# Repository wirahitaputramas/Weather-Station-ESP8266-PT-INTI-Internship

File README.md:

# Weather Station ESP8266

# Overview

<div align="center">
  
</div>
<div align="center">
  
</div>

<div align="center">
  
</div>
<div align="center">
  
</div>

The repository includes everything needed to build an Weather Station ESP8266 (including hardware information, PCB Design, and footprint):

# What do I Need To Make One?
In this project, we assume that we still need to debug and see the output in serial monitor. So we need :
- Arduino IDE (the lastest version recommended) with serial monitor in PC or Laptop

Other Essential Things :
- Standar USB to Micro USB cable
- ESP-12E Development Board ESP8266 NodeMCU ([Pict](https://raw.githubusercontent.com/wirahitaputramas/Weather-Station-ESP8266-PT-INTI-Internship/master/images/ESP%2012E%20Development%20Board.jpg "ESP-12E Development Board ESP8266 NodeMCU"))
- OLED I2C Display 128x64 Pixel ([Pict](https://raw.githubusercontent.com/wirahitaputramas/Weather-Station-ESP8266-PT-INTI-Internship/master/images/OLED%20I2C%20Display.jpg "OLED I2C Display 128x64 Pixel"))
- SPI MicroSD Module ([Pict](https://raw.githubusercontent.com/wirahitaputramas/Weather-Station-ESP8266-PT-INTI-Internship/master/images/MicroSD%20Modul.jpg "MicroSD Module"))
- MicroSD Card (SDHC Under 32 GB recommended)
- DHT22 Modue ([Pict](https://raw.githubusercontent.com/wirahitaputramas/Weather-Station-ESP8266-PT-INTI-Internship/master/images/DHT22%20Module.jpgg "DHT22 Module"))
- LDR Photoresistor
- SMD Resistor 5 kohm

# How to Make One ?

## Testing and Prototyping on Breadboard
Before we make the circuit on the PCB, we must ensure that we choose the correct GPIO. Because of that, first of all we must hookup all component on breadboard like this picture below :
<div align="center">
  
</div>

Here is the raw fritzing file ([Fritzing](https://github.com/wirahitaputramas/Weather-Station-ESP8266-PT-INTI-Internship/blob/master/Weather%20Station%20ESP8266%20on%20Breadboard.fzz "Weather Station ESP8266 on Breadboard"))

Here is the connection of each pin (exclude Vcc & GND) :
- D1 or GPIO5 to OLED SCL
- D2 or GPIO4 to OLED SDA
- D4 or GPIO2 to DHT22 IO (Data)
- D5 or GPIO14 to microSD SCLK
- D6 or GPIO12 to microSD MISO
- D7 or GPIO13 to microSD MOSI
- D8 or GPIO15 to microSD CS
- A0 or ADC0 to LDR Photoresistor

After finish the wiring, just prepare to upload the arduino whole program. We will modify any part of the source code in this repository

1. make sure that you have included the NTP Library from Fabrice Weinberg in the same folder with .ino file. Here is the [NTP Library Fabrice Weinberg](https://github.com/arduino-libraries/NTPClient.git "NTP Library Fabrice Weinberg")

2. Write down your WiFi Accses Point identity in IoT Property Block Code

```
/* IoT Property */
#include <ESP8266WiFi.h>
const char *ssid =  "SSID";     // replace with your wifi ssid and wpa2 key
const char *pass =  "PASS";
WiFiClient client;
```
3. Make your project channel in Thingspeak platform. Allocate three fields to store three different sensor reading data. After that get your channel ID and API key of your project channel. In the Screenshot below, the blue scratch is the channel ID, and the red scratch is the API Key
<div align="center">
  
</div>

Write down your Thingspeak Channel identity in Thingspeak Property Block Code in the source code.ino
```
/* Thingspeak Property */
#include <ThingSpeak.h>
unsigned long myChannelNumber = 823396; //Replace with your channel number
const char * myWriteAPIKey = "API KEY"; //Replace with your API key
/* End of Thingspeak Property */
```

4. Make sure all of pin assign in the source code.ino related to your wiring on breadboard

5. After finish uploading the program. Open the serial monitor and set the baud rate at 115200. Make sure there's no "nan" value. The nan value sometimes appear at DHT22 reading value. To Fix that, just try to plug and unplug again the DHT22 until the exact value appear, or you can trigger the DHT22 by connecting the Vcc pin to 5V

## PCB Desain, Assembly The Final Design, And Run the Weather Station on PCB

After the Prototyping on breadboard finish, now we can design the PCB on KiCad. 

1. First you need to make the Schematic or diagram of your circuit including the connection between each pin in ESP8266 and all the others component.

In this repo, you can get all file you need if you just want to skip this step. Find all .lib files. Those are your symbol schematic library. Our team have made those symbols from the scratch by seeing the datasheet and the real component. But we strongly recommended to learn and try make your own symbol because sometimes the symbol library from the other author doesn't match with your real component, usually it's pin arrangement. This is our schematic
<div align="center">
  
</div>

Use the label method instead of wiring method to make connection between each pin and don't forget to give some outline and comment information

2. Test The connection, and if no error, assign the footprint of each component
In this repo, we have included all footprint of the project, so you can just find the .preety folder and use that. Please note that our concept in this project is just soldering some female pin socket instead of directly solder each pin of component. So in the future, if the component broken you can easily replace with the other new one.

3. Placing and Tracking the PCB
Actually, this process depend on your own preference in placing and route the PCB. It isn't a problem if you try this step and find that your PCB is different with our PCB below, because the importnt things is all ratnest disappear and all the pin connection is right

<div align="center">
  
</div>

We choose a single layer instead of double layer because in our place double layer PCB more exspensive even when you compare with a huge single layer PCB. And also in our place, The manufacture and Printing Machine only support minimum track size at 0.6 mm and hole or drill diameter at 0.4 mm

4. After Finish the PCB. Generate the Greber File (as already available in this repo). Those picture below are some configuration to generate the gerber and drill file of our PCB
<div align="center">
  
</div>
<div align="center">
  
</div>

5. Print the PCB with Gerber File. Actually I just give those gerber and drill file and don't know the exact process of PCB printing. But i see the PCB printing employee use corel draw to process the greber file.

This first image is our PCB before soldering process
<div align="center">
  
</div>

<div align="center">
  
</div>

The  image is our PCB after soldering process

<div align="center">
  
</div>

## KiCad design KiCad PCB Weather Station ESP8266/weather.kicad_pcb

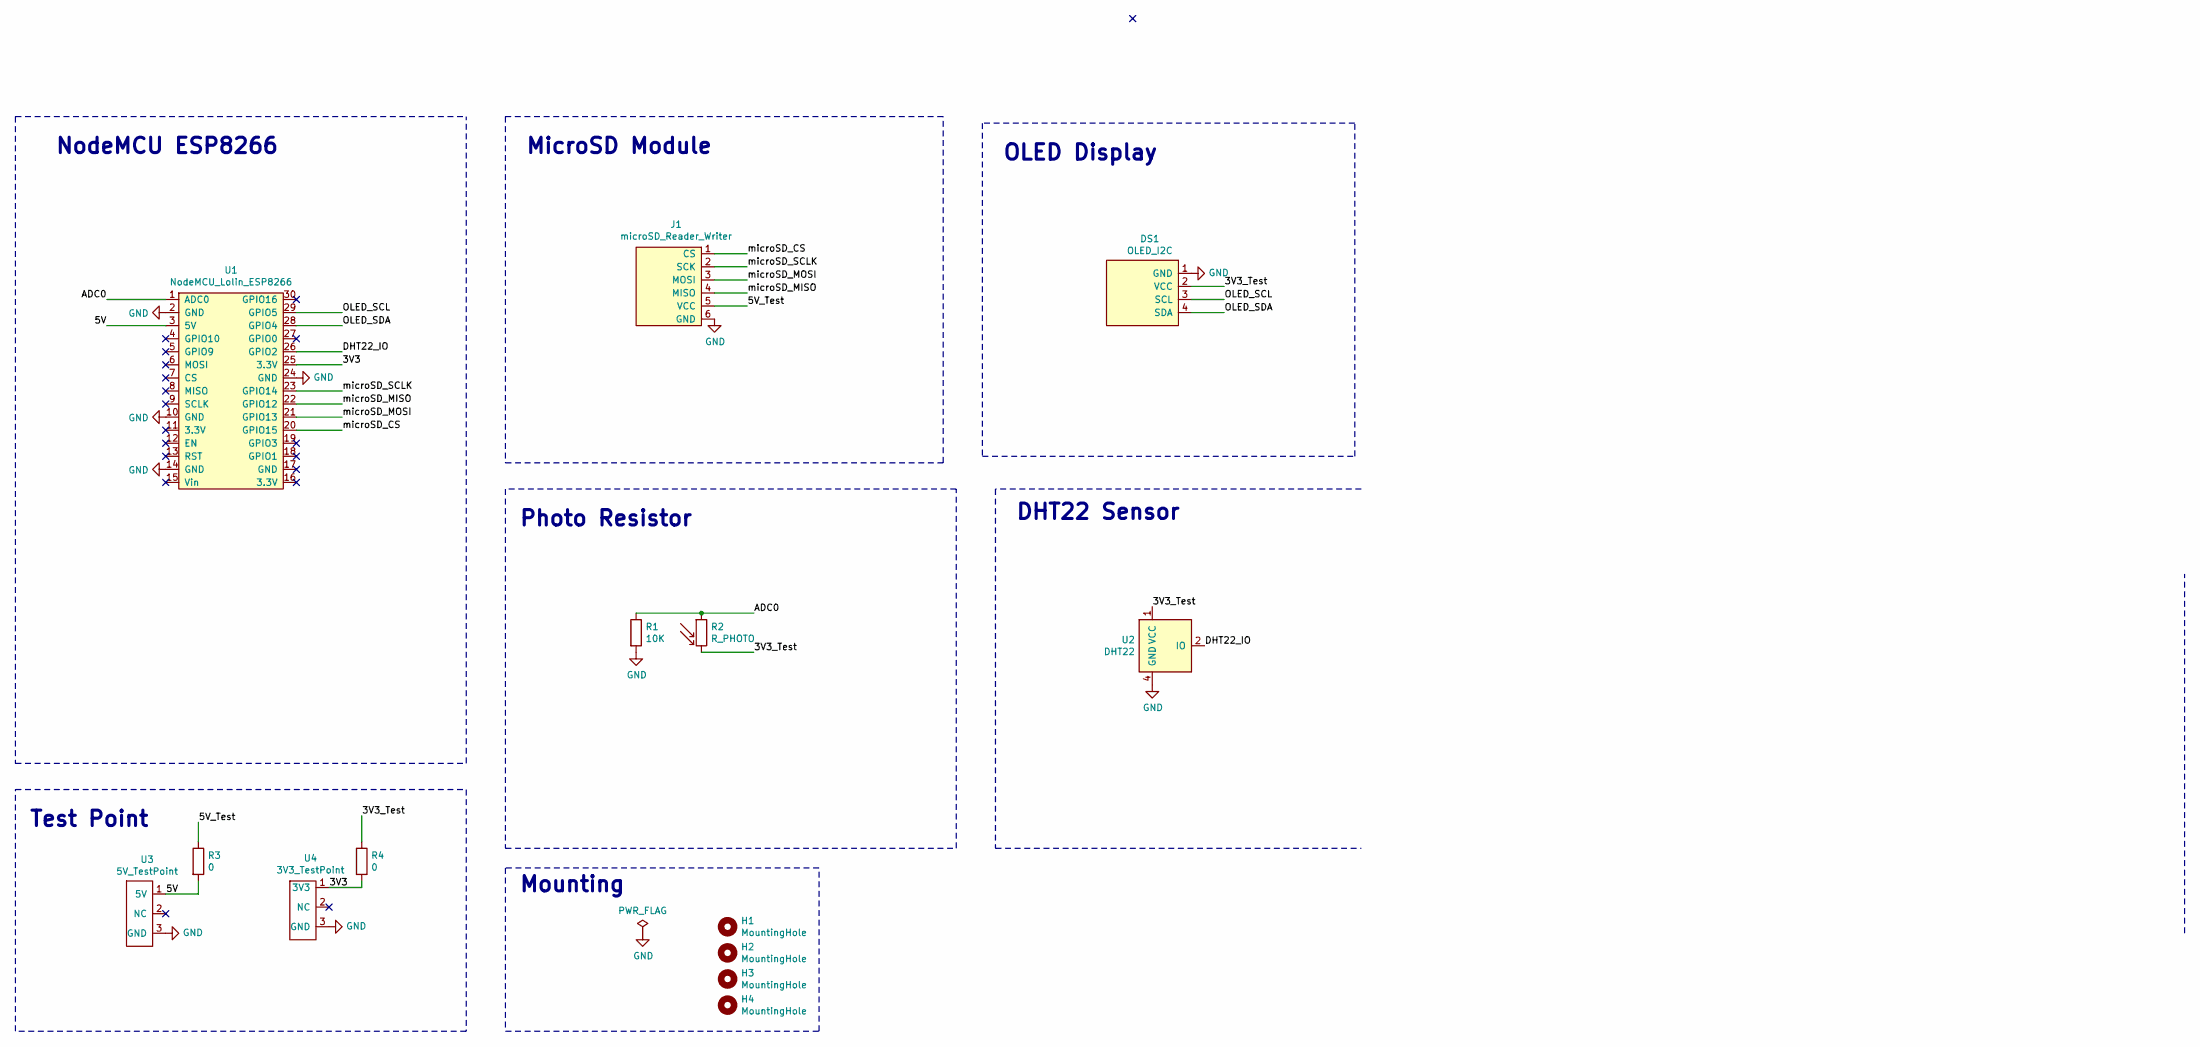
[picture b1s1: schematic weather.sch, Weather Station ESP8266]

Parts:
DS1: OLED_I2C
H1, H2, H3, H4: MountingHole; MountingHole_3.2mm_M3_DIN965
J1: microSD_Reader_Writer; MicroSD_Card_Modul
R1: 10K; R_0805_2012Metric
R2: R_PHOTO; PhotoResistor_THT_Horizontal
R3, R4: 0; R_0805_2012Metric
U1: NodeMCU_Lolin_ESP8266; NodeMCU_ESP8266
U2: DHT22
U3: 5V_TestPoint; PinSocket_1x03_P2.54mm_Vertical
U4: 3V3_TestPoint; PinSocket_1x03_P2.54mm_Vertical

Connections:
/3V3: R4.2, U1.25 (3.3V), U4.1 (3V3)
/3V3_Test: DS1.2 (VCC), R2.2, R4.1, U2.1 (VCC)
/5V: R3.2, U1.3 (5V), U3.1 (5V)
/5V_Test: J1.5 (VCC), R3.1
/ADC0: R1.1, R2.1, U1.1 (ADC0)
/DHT22_IO: U1.26 (GPIO2), U2.2 (IO)
/OLED_SCL: DS1.3 (SCL), U1.29 (GPIO5)
/OLED_SDA: DS1.4 (SDA), U1.28 (GPIO4)
/microSD_CS: J1.1 (CS), U1.20 (GPIO15)
/microSD_MISO: J1.4 (MISO), U1.22 (GPIO12)
/microSD_MOSI: J1.3 (MOSI), U1.21 (GPIO13)
/microSD_SCLK: J1.2 (SCK), U1.23 (GPIO14)
GND: DS1.1 (GND), J1.6 (GND), R1.2, U1.2 (GND), U1.10 (GND), U1.14 (GND), U1.24 (GND), U2.4 (GND), U3.3 (GND), U4.3 (GND)

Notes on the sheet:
NodeMCU ESP8266
MicroSD Module
OLED Display
DHT22 Sensor
Photo Resistor
Test Point
Mounting

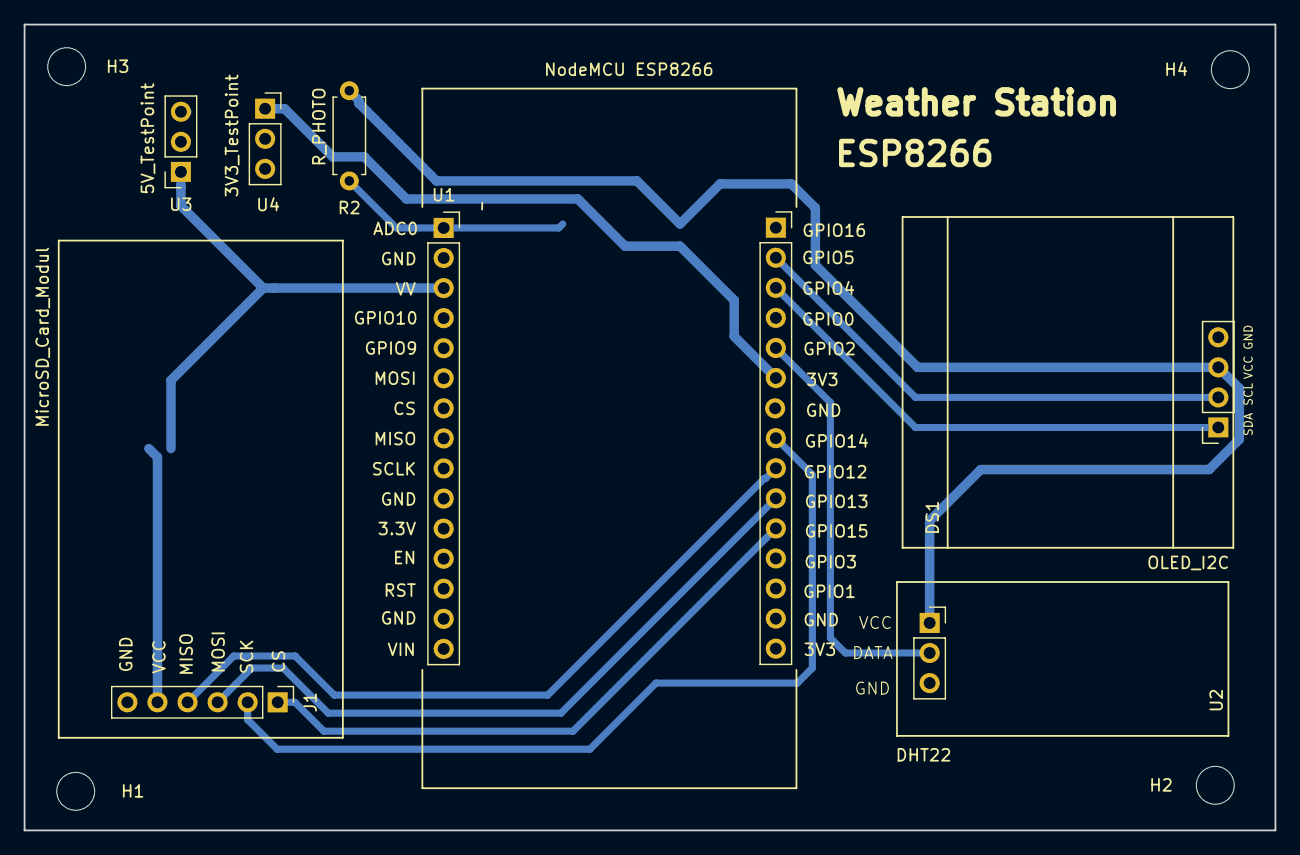
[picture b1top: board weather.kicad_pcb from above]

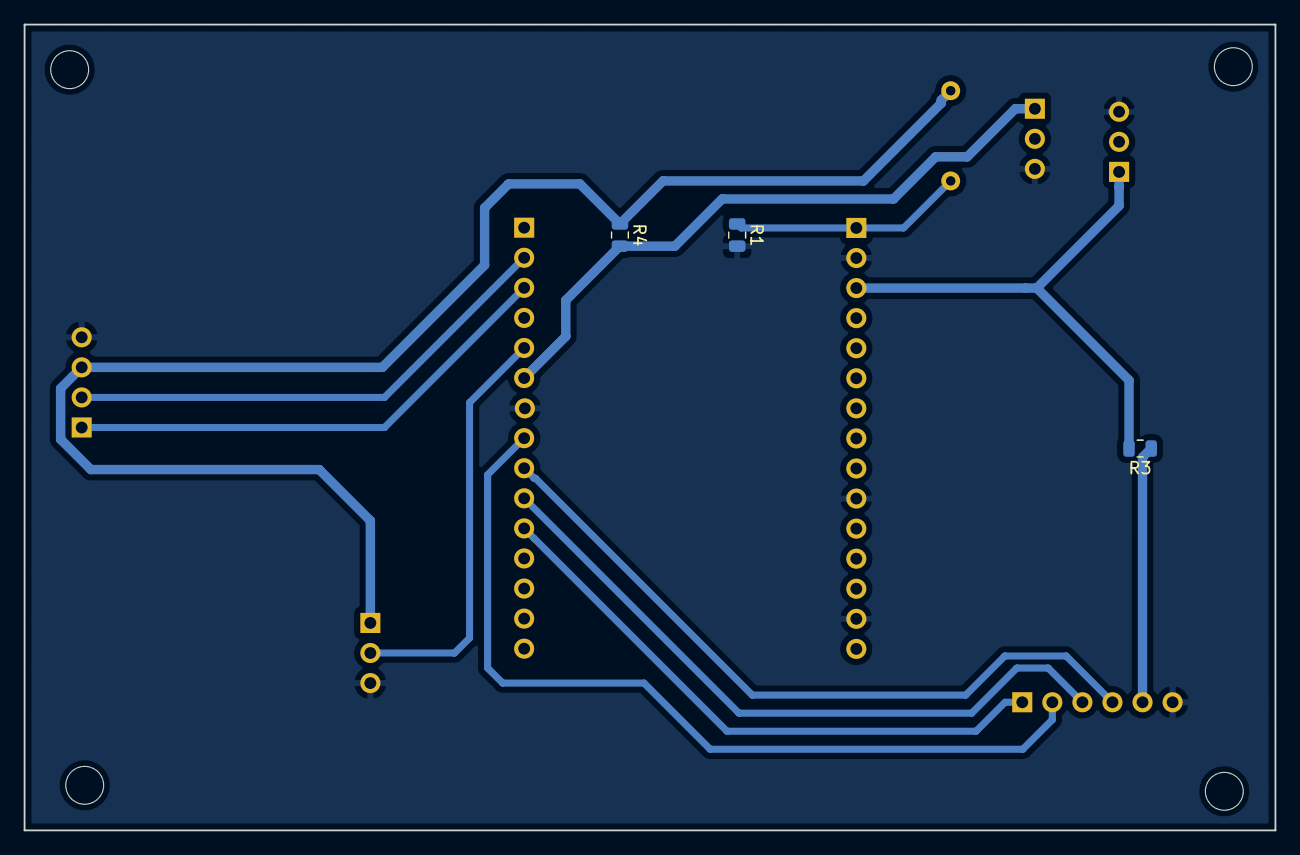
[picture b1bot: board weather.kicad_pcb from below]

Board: 2 copper layers, 105.7 x 68.1 mm, 14 parts (3 on the bottom side), 13 nets.

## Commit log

2019-07-27 Create Place NTP Library Fabrice Weinberg In This Folder !
2019-07-27 Rename Place NTP Library Fabrice Weinberg In This Folder ! to Place NTP Library Fabrice Weinberg In This Folder !.txt
